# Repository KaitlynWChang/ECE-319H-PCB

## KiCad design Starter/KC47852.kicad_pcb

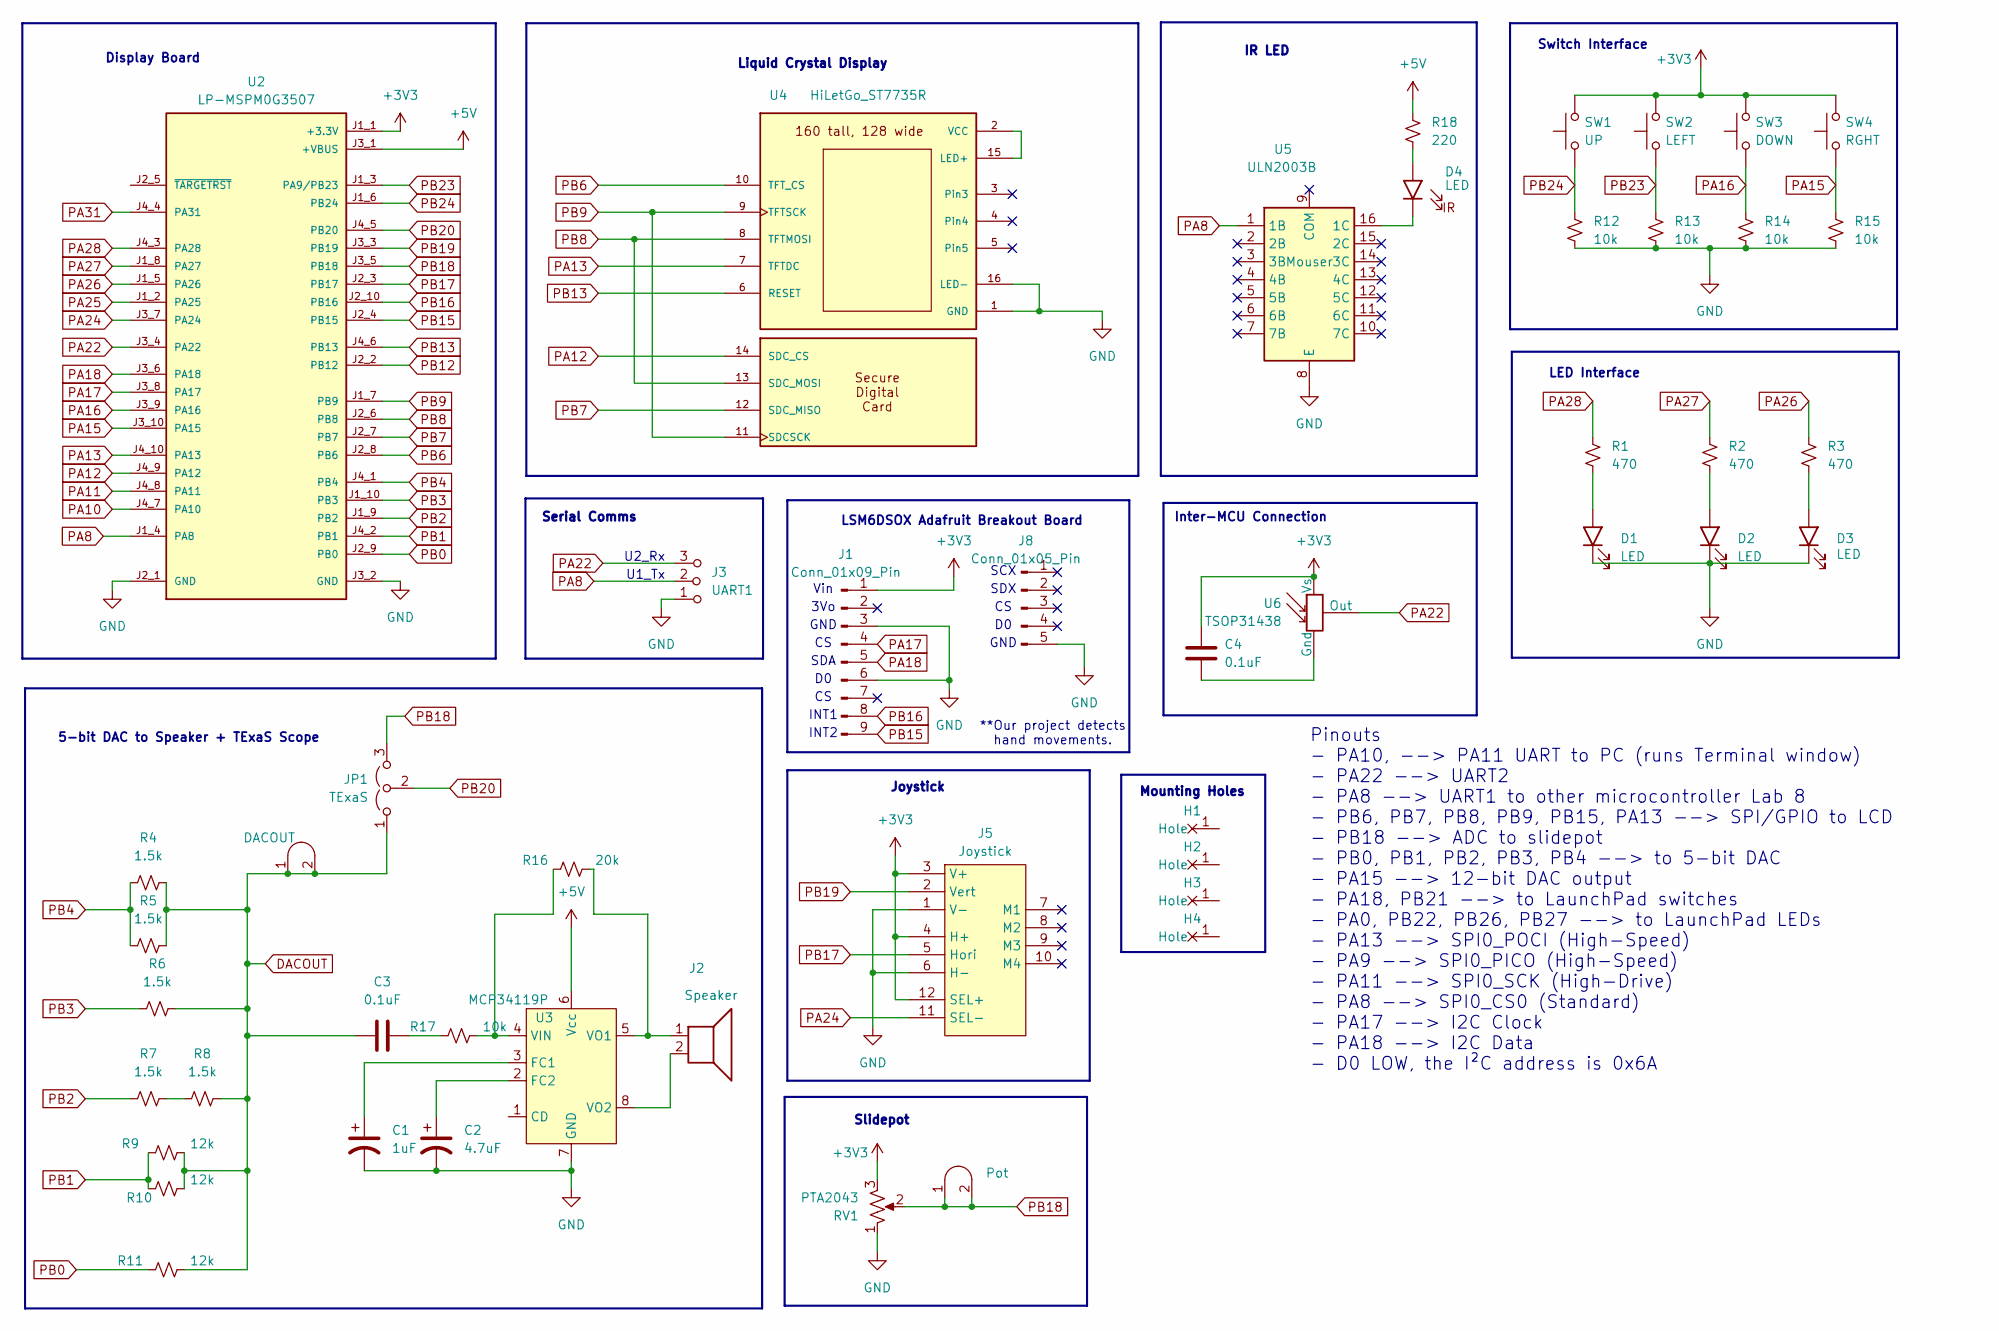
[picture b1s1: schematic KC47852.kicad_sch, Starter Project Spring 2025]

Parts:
C1: 1uF; CP_Radial_Tantal200mil
C2: 4.7uF; CP_Radial_Tantal200mil
C3, C4: 0.1uF; C_Axial_200mil
D1, D2, D3, D4: LED; LED_D5.0mm
H1, H2, H3, H4: MountingHole_4_40
J1: Conn_01x09_Pin; PinHeader_1x09_P2.54mm_Vertical
J2: Speaker; PinHeader_1x02_P2.54mm_Vertical
J3: UART1; PinHeader_1x03_P2.54mm_Vertical
J4: Pot; Testpoint_1x02_P2.54mm
J5: Joystick; SparkfunJoystick
J7: DACOUT; Testpoint_1x02_P2.54mm
J8: Conn_01x05_Pin; PinHeader_1x05_P2.54mm_Vertical
JP1: TExaS; PinHeader_1x03_P2.54mm_Vertical
R1, R2, R3: 470; R_Axial_DIN0204_L3.6mm_D1.6mm_P7.62mm_Horizontal
R4, R5, R6, R7, R8: 1.5k; R_Axial_DIN0204_L3.6mm_D1.6mm_P7.62mm_Horizontal
R9, R10, R11: 12k; R_Axial_DIN0204_L3.6mm_D1.6mm_P7.62mm_Horizontal
R12, R13, R14, R15, R17: 10k; R_Axial_DIN0204_L3.6mm_D1.6mm_P7.62mm_Horizontal
R16: 20k; R_Axial_DIN0204_L3.6mm_D1.6mm_P7.62mm_Horizontal
R18: 220; R_Axial_DIN0204_L3.6mm_D1.6mm_P7.62mm_Horizontal
RV1: PTA2043; PTA2043pot
SW1: UP; SW_PUSH_6mm
SW2: LEFT; SW_PUSH_6mm
SW3: DOWN; SW_PUSH_6mm
SW4: RGHT; SW_PUSH_6mm
U2: LP-MSPM0G3507; ti_LP_MSPM0G3507
U3: MCP34119P; DIP-8_W7.62mm_LongPads
U4: HiLetGo_ST7735R; hiletgo_st7735r
U5: ULN2003B; DIP-16_W7.62mm
U6: TSOP31438

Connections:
+3V3: C4.1, J1.1, J5.3 (V+), J5.4 (H+), J5.12 (SEL+), RV1.3, SW1.2, SW2.2, SW3.2, SW4.2, U2.J1_1 (+3.3V), U6.2 (Vs)
+5V: R18.1, U2.J3_1 (+VBUS), U3.6 (Vcc)
DACOUT: C3.1, J7.1 (A), J7.2 (B), JP1.1 (A), R4.1, R5.1, R6.1, R8.1, R9.1, R10.1, R11.1
GND: C1.2, C2.2, D1.1 (K), D2.1 (K), D3.1 (K), J1.3, J1.6, J3.1 (A), J5.1 (V-), J5.6 (H-), J8.5, R12.2, R13.2, R14.2, R15.2, RV1.1, U2.J2_1 (GND), U2.J3_2 (GND), U3.7 (GND), U4.1 (GND), U4.16 (LED-), U5.8 (E)
unnamed: C3.2, R17.2
unnamed: D1.2 (A), R1.2
unnamed: D2.2 (A), R2.2
unnamed: D3.2 (A), R3.2
unnamed: D4.2 (A), R18.2
unnamed: D4.1 (K), U5.16 (1C)
unnamed: R7.1, R8.2
unnamed: C1.1, U3.3 (FC1)
unnamed: C2.1, U3.2 (FC2)
unnamed: R16.2, R17.1, U3.4 (VIN)
unnamed: J2.1, R16.1, U3.5 (VO1)
unnamed: J2.2, U3.8 (VO2)
unnamed: U4.2 (VCC), U4.15 (LED+)
unnamed: C4.2, U6.1 (Gnd)
PA8: J3.2 (B), U2.J1_4 (PA8), U5.1 (1B)
PA10: U2.J4_7 (PA10)
PA11: U2.J4_8 (PA11)
PA12: U2.J4_9 (PA12), U4.14 (SDC_CS)
PA13: U2.J4_10 (PA13), U4.7 (TFTDC)
PA15: R15.1, SW4.1, U2.J3_10 (PA15)
PA16: R14.1, SW3.1, U2.J3_9 (PA16)
PA17: J1.4, U2.J3_8 (PA17)
PA18: J1.5, U2.J3_6 (PA18)
PA22: J3.3 (C), U2.J3_4 (PA22), U6.3 (Out)
PA24: J5.11 (SEL-), U2.J3_7 (PA24)
PA25: U2.J1_2 (PA25)
PA26: R3.1, U2.J1_5 (PA26)
PA27: R2.1, U2.J1_8 (PA27)
PA28: R1.1, U2.J4_3 (PA28)
PA31: U2.J4_4 (PA31)
PB0: R11.2, U2.J2_9 (PB0)
PB1: R9.2, R10.2, U2.J4_2 (PB1)
PB2: R7.2, U2.J1_9 (PB2)
PB3: R6.2, U2.J1_10 (PB3)
PB4: R4.2, R5.2, U2.J4_1 (PB4)
PB6: U2.J2_8 (PB6), U4.10 (TFT_CS)
PB7: U2.J2_7 (PB7), U4.12 (SDC_MISO)
PB8: U2.J2_6 (PB8), U4.8 (TFTMOSI), U4.13 (SDC_MOSI)
PB9: U2.J1_7 (PB9), U4.9 (TFTSCK), U4.11 (SDCSCK)
PB12: U2.J2_2 (PB12)
PB13: U2.J4_6 (PB13), U4.6 (RESET)
PB15: J1.9, U2.J2_4 (PB15)
PB16: J1.8, U2.J2_10 (PB16)
PB17: J5.5 (Hori), U2.J2_3 (PB17)
PB18: J4.1 (A), J4.2 (B), JP1.3 (B), RV1.2, U2.J3_5 (PB18)
PB19: J5.2 (Vert), U2.J3_3 (PB19)
PB20: JP1.2 (C), U2.J4_5 (PB20)
PB23: R13.1, SW2.1, U2.J1_3 (PA9/PB23)
PB24: R12.1, SW1.1, U2.J1_6 (PB24)

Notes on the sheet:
Slidepot
SCX
IR LED
Joystick
Display Board
5-bit DAC to Speaker + TExaS Scope
Mounting Holes
INT1
U2_Rx
SDA
Pinouts - PA10, --> PA11 UART to PC (runs Terminal window) - PA22 --> UART2 - PA8 --> UART1 to other microcontroller Lab 8 - PB6, PB7, PB8, PB9, PB15, PA13 --> SPI/GPIO to LCD - PB18 --> ADC to slidepot - PB0, PB1, PB2, PB3, PB4 --> to 5-bit DAC - PA15 --> 12-bit DAC output - PA18, PB21 --> to Laun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
GND
U1_Tx
3Vo
INT2
Vin
LSM6DSOX Adafruit Breakout Board
Inter-MCU Connection
Serial Comms
SDX
Switch Interface
Liquid Crystal Display
**Our project detects hand movements.
LED Interface

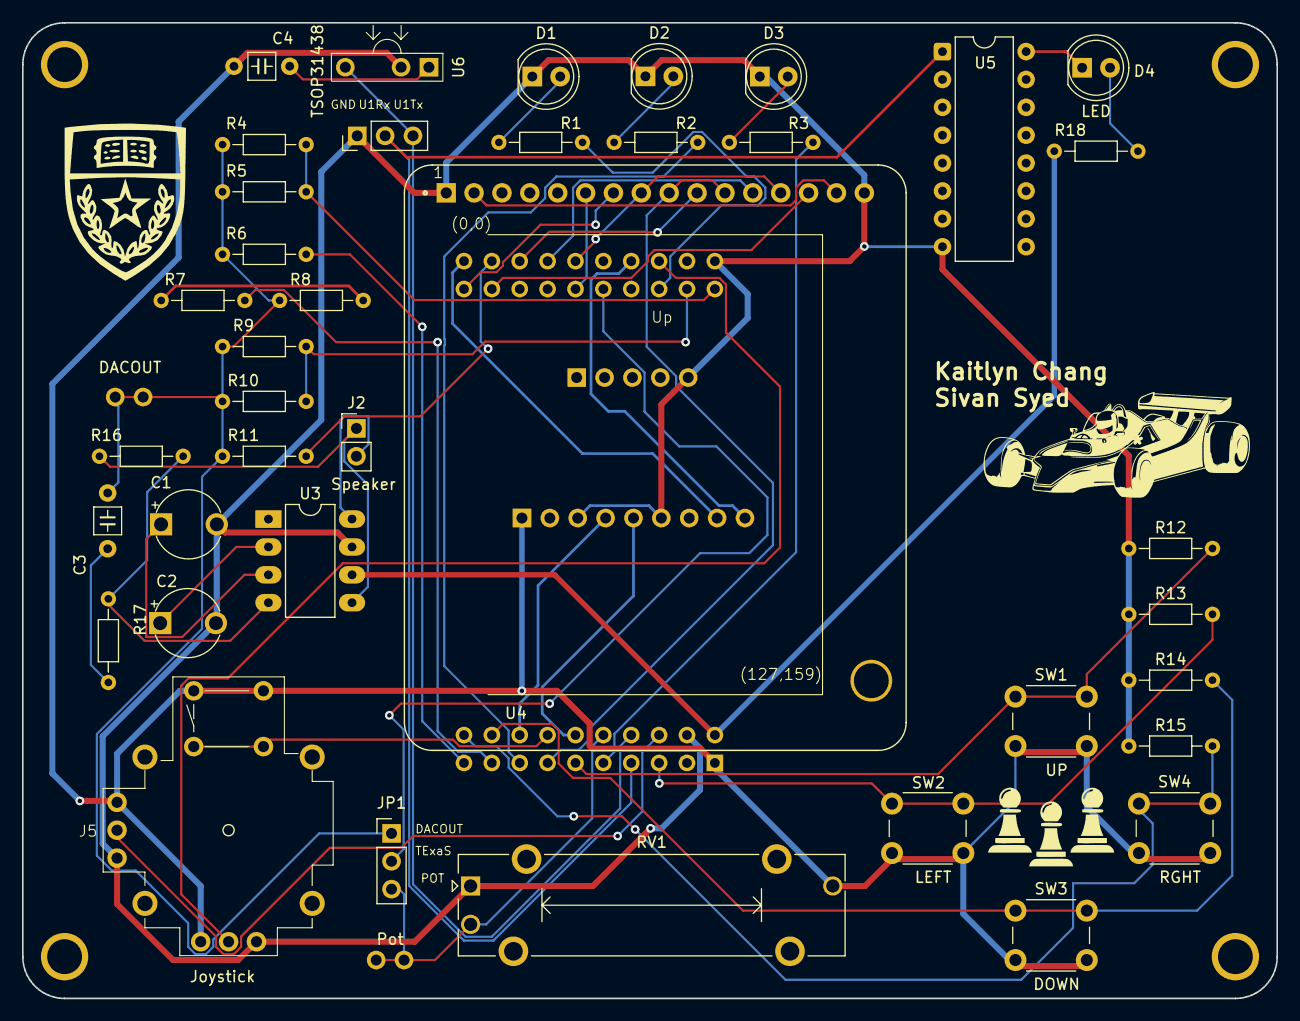
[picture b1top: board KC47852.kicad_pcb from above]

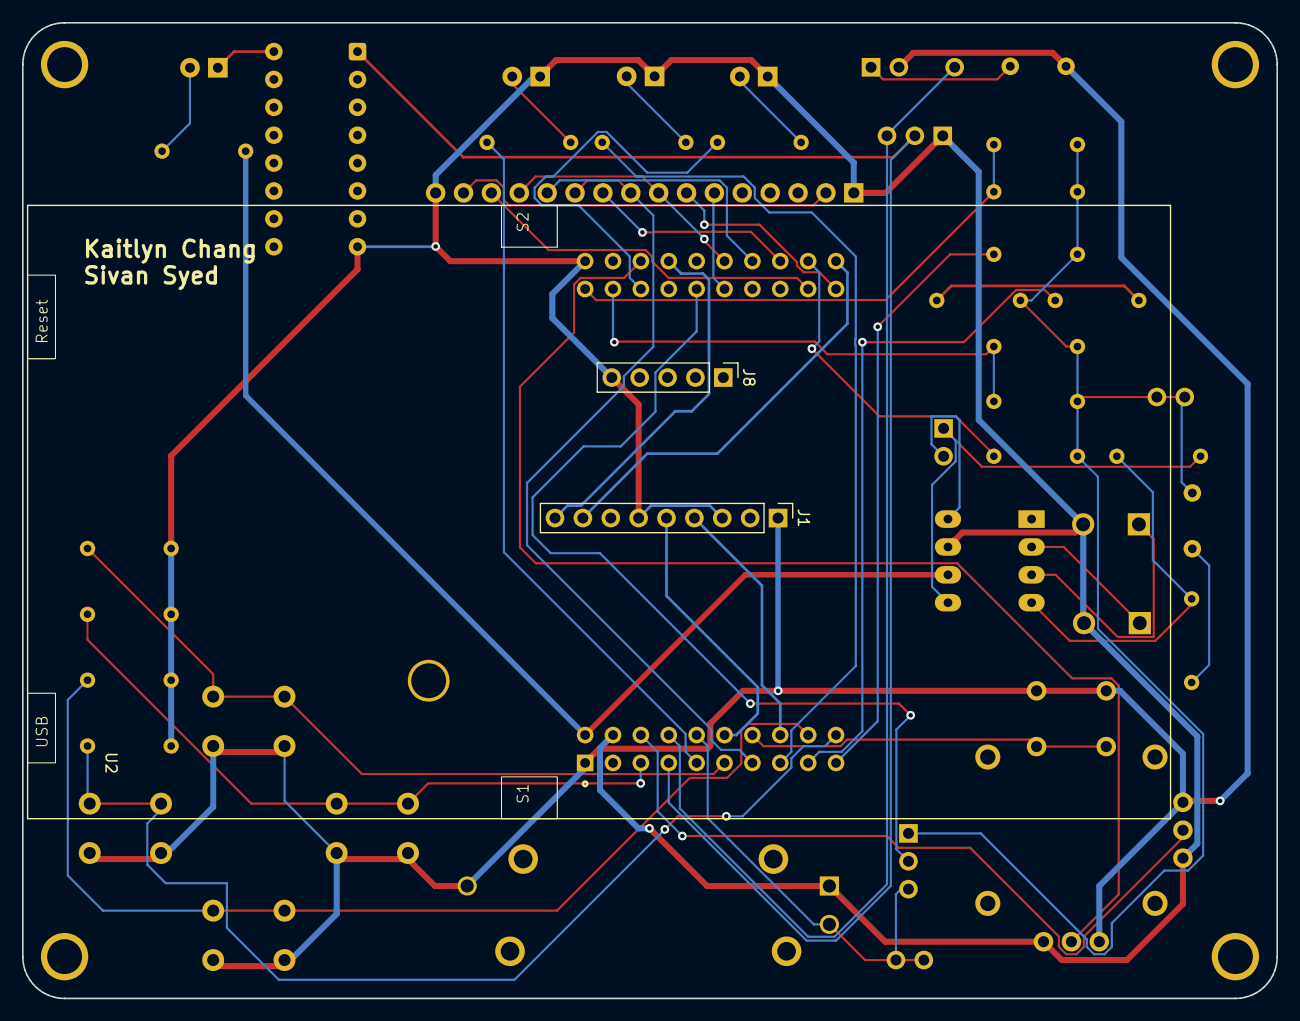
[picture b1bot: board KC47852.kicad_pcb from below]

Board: 2 copper layers, 114.3 x 88.9 mm, 48 parts (3 on the bottom side), 48 nets.

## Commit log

2025-03-20 Project initialization
2025-03-20 Wired LEDs, Switches, DAC, and Jumper
2025-03-20 319H Components
2025-03-20 Wired audio amplifier. Referenced page 8 of Datasheet. PLEASE DOUBLE CHECK WORK
2025-03-22 Reformatting and added cross-board wiring as well as IMU
2025-03-23 Minor changes!
2025-03-23 Minor edits V2!
2025-03-23 layout
2025-03-23 bruh
2025-04-12 we did a thing
